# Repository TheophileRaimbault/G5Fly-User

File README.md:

# G5Fly STM32G473

Open-source GNSS navigation board for drones and robotics.

G5Fly is a compact GNSS board built around the Septentrio Mosaic-G5 module and an STM32G473 microcontroller. This branch contains the STM32 hardware design and AP_Periph firmware configuration for DroneCAN integration.

Author: <a href="https://github.com/TheophileRaimbault">Théophile Raimbault</a><br>
Maintainer: Septentrio GNSS GitHub user <githubuser@septentrio.com><br>
External website: https://github.com/septentrio-gnss/G5Fly<br>
License: <a href="https://creativecommons.org/licenses/by-sa/4.0/">Creative Commons Attribution-ShareAlike 4.0</a> and <a href="https://www.oshwa.org/definition/">Open Source Hardware</a><br>

<div style="background-color:#e3f2fd; border-left:5px solid #1976D2; padding:10px; border-radius:5px; margin-top:10px;">
  ℹ️ <strong>Note:</strong> G5Fly is optimized for a 30.5 x 30.5 mm FPV drone form factor and is intended for open source drone or robot projects.
</div><br>

STM32 schematic: [Resources/G5Fly-schematics-STM32.pdf](Resources/G5Fly-schematics-STM32.pdf)

## Who is this repository for?

This project serves two audiences:

- Users who want to buy, assemble, or use the board as-is.
- Designers who want to understand the hardware in detail and create a custom version.

If you are a user, start with the sections below. If you want to modify the design, go to [DESIGN.md](DESIGN.md).

## For users

### Key features
- Compact 30.5 x 30.5 mm FPV-friendly form factor
- Septentrio Mosaic-G5 GNSS receiver support
- USB and external 5 V power options
- DroneCAN, TTL, serial and I2C interfaces
- Reset input and status LEDs
- STM32G473-based AP_Periph node with DroneCAN support

### Quick start
1. Use the current production design files in [hardware/versions/v1/kicad/production](hardware/versions/v1/kicad/production/) if you want to build the board without changing the design.
2. Connect a suitable GNSS antenna and power the board through USB or an external 5 V source.
3. Build and flash the AP_Periph firmware using the configuration in [firmware](firmware/).
4. Use the available UART, I2C, or DroneCAN interfaces depending on your integration target.
5. Validate the board with the status LEDs and the expected GNSS fix behavior before full integration.

### Antenna and power
- Power the board according to the STM32 schematic and the regulator design.
- Use an active antenna only with the voltage specified by the antenna manufacturer.
- Verify antenna power selection and connector wiring before powering the board.

<div style="background-color:#ffebee; border-left:5px solid #c62828; padding:10px; border-radius:5px; margin:10px 0;">
  <strong>Warning:</strong> Solder <code>JP1</code> before using an active antenna. If the jumper is left open, the <code>VANT</code> net is not powered and the antenna may not work, causing a significant loss of GNSS performance. Select only one voltage according to the antenna datasheet.
</div>

<table>
  <tr>
    <td align="center"><br><strong>3.3 V antenna</strong><br>Connect <code>VANT</code> to <code>+3.3V_RF</code>.</td>
    <td align="center"><br><strong>5 V antenna</strong><br>Connect <code>VANT</code> to <code>+5V</code>.</td>
  </tr>
</table>

### Production and manufacturing
For a production build without hardware changes:

- Use the current KiCad project and generated manufacturing files from the hardware folder: [hardware/versions/v1/kicad](hardware/versions/v1/kicad/)
- Provide the manufacturer with the schematic, PCB files, BOM, and CPL.
- Verify antenna connector type, jumper configuration, and power options before assembly.
- Reference schematic: [Resources/G5Fly-schematics-STM32.pdf](Resources/G5Fly-schematics-STM32.pdf)

#### JLCPCB manufacturing requirements

- Keep the default KiCad PCB setup and its calculated impedance settings.
- Manufacture the board as a 6-layer PCB.
- `PCB Requirement: User.1 layer should be used as the V-cut guide layer.`
- Refer to the PCB design rules in [hardware/common/design_rules/design-rules.md](hardware/common/design_rules/design-rules.md) when preparing or reviewing the PCB for production.
- Use the [G5Fly_STM32_Rev2_JLCPCB production archive](hardware/versions/v1/kicad/production/G5Fly_STM32_Rev2_JLCPCB.zip) for the files prepared specifically for manufacturing at JLCPCB.

### Power and antenna
- Keep GNSS antenna cables away from noisy power traces where possible.

### Recommended antenna options
The following antenna families are commonly considered for evaluation:

- D-Helix antenna HX-CHX600A
- D-Helix antenna HX-CH7609A
- HC990EXF Calian antenna

A SMA-to-MMCX adapter is often useful for compatibility with the board connector.

## For designers and contributors

The detailed hardware design guide is available in [DESIGN.md](DESIGN.md).

That document covers:
- Overall architecture and major blocks
- Component selection and board organization
- How to create a custom derivative board
- Manufacturing and validation recommendations
- AP_Periph firmware configuration and DroneCAN bring-up

## Repository structure
- [hardware](hardware): PCB sources, KiCad projects, and mechanical assets
- [firmware](firmware): firmware and configuration files
- [Resources](Resources): images, schematics, and support documents
- [firmware/DroneCAN-Setup.md](firmware/DroneCAN-Setup.md): AP_Periph, DroneCAN, Mission Planner, and debugging procedure

## Licensing
This project is released under the Creative Commons Attribution-ShareAlike 4.0 license and follows the Open Source Hardware definition.

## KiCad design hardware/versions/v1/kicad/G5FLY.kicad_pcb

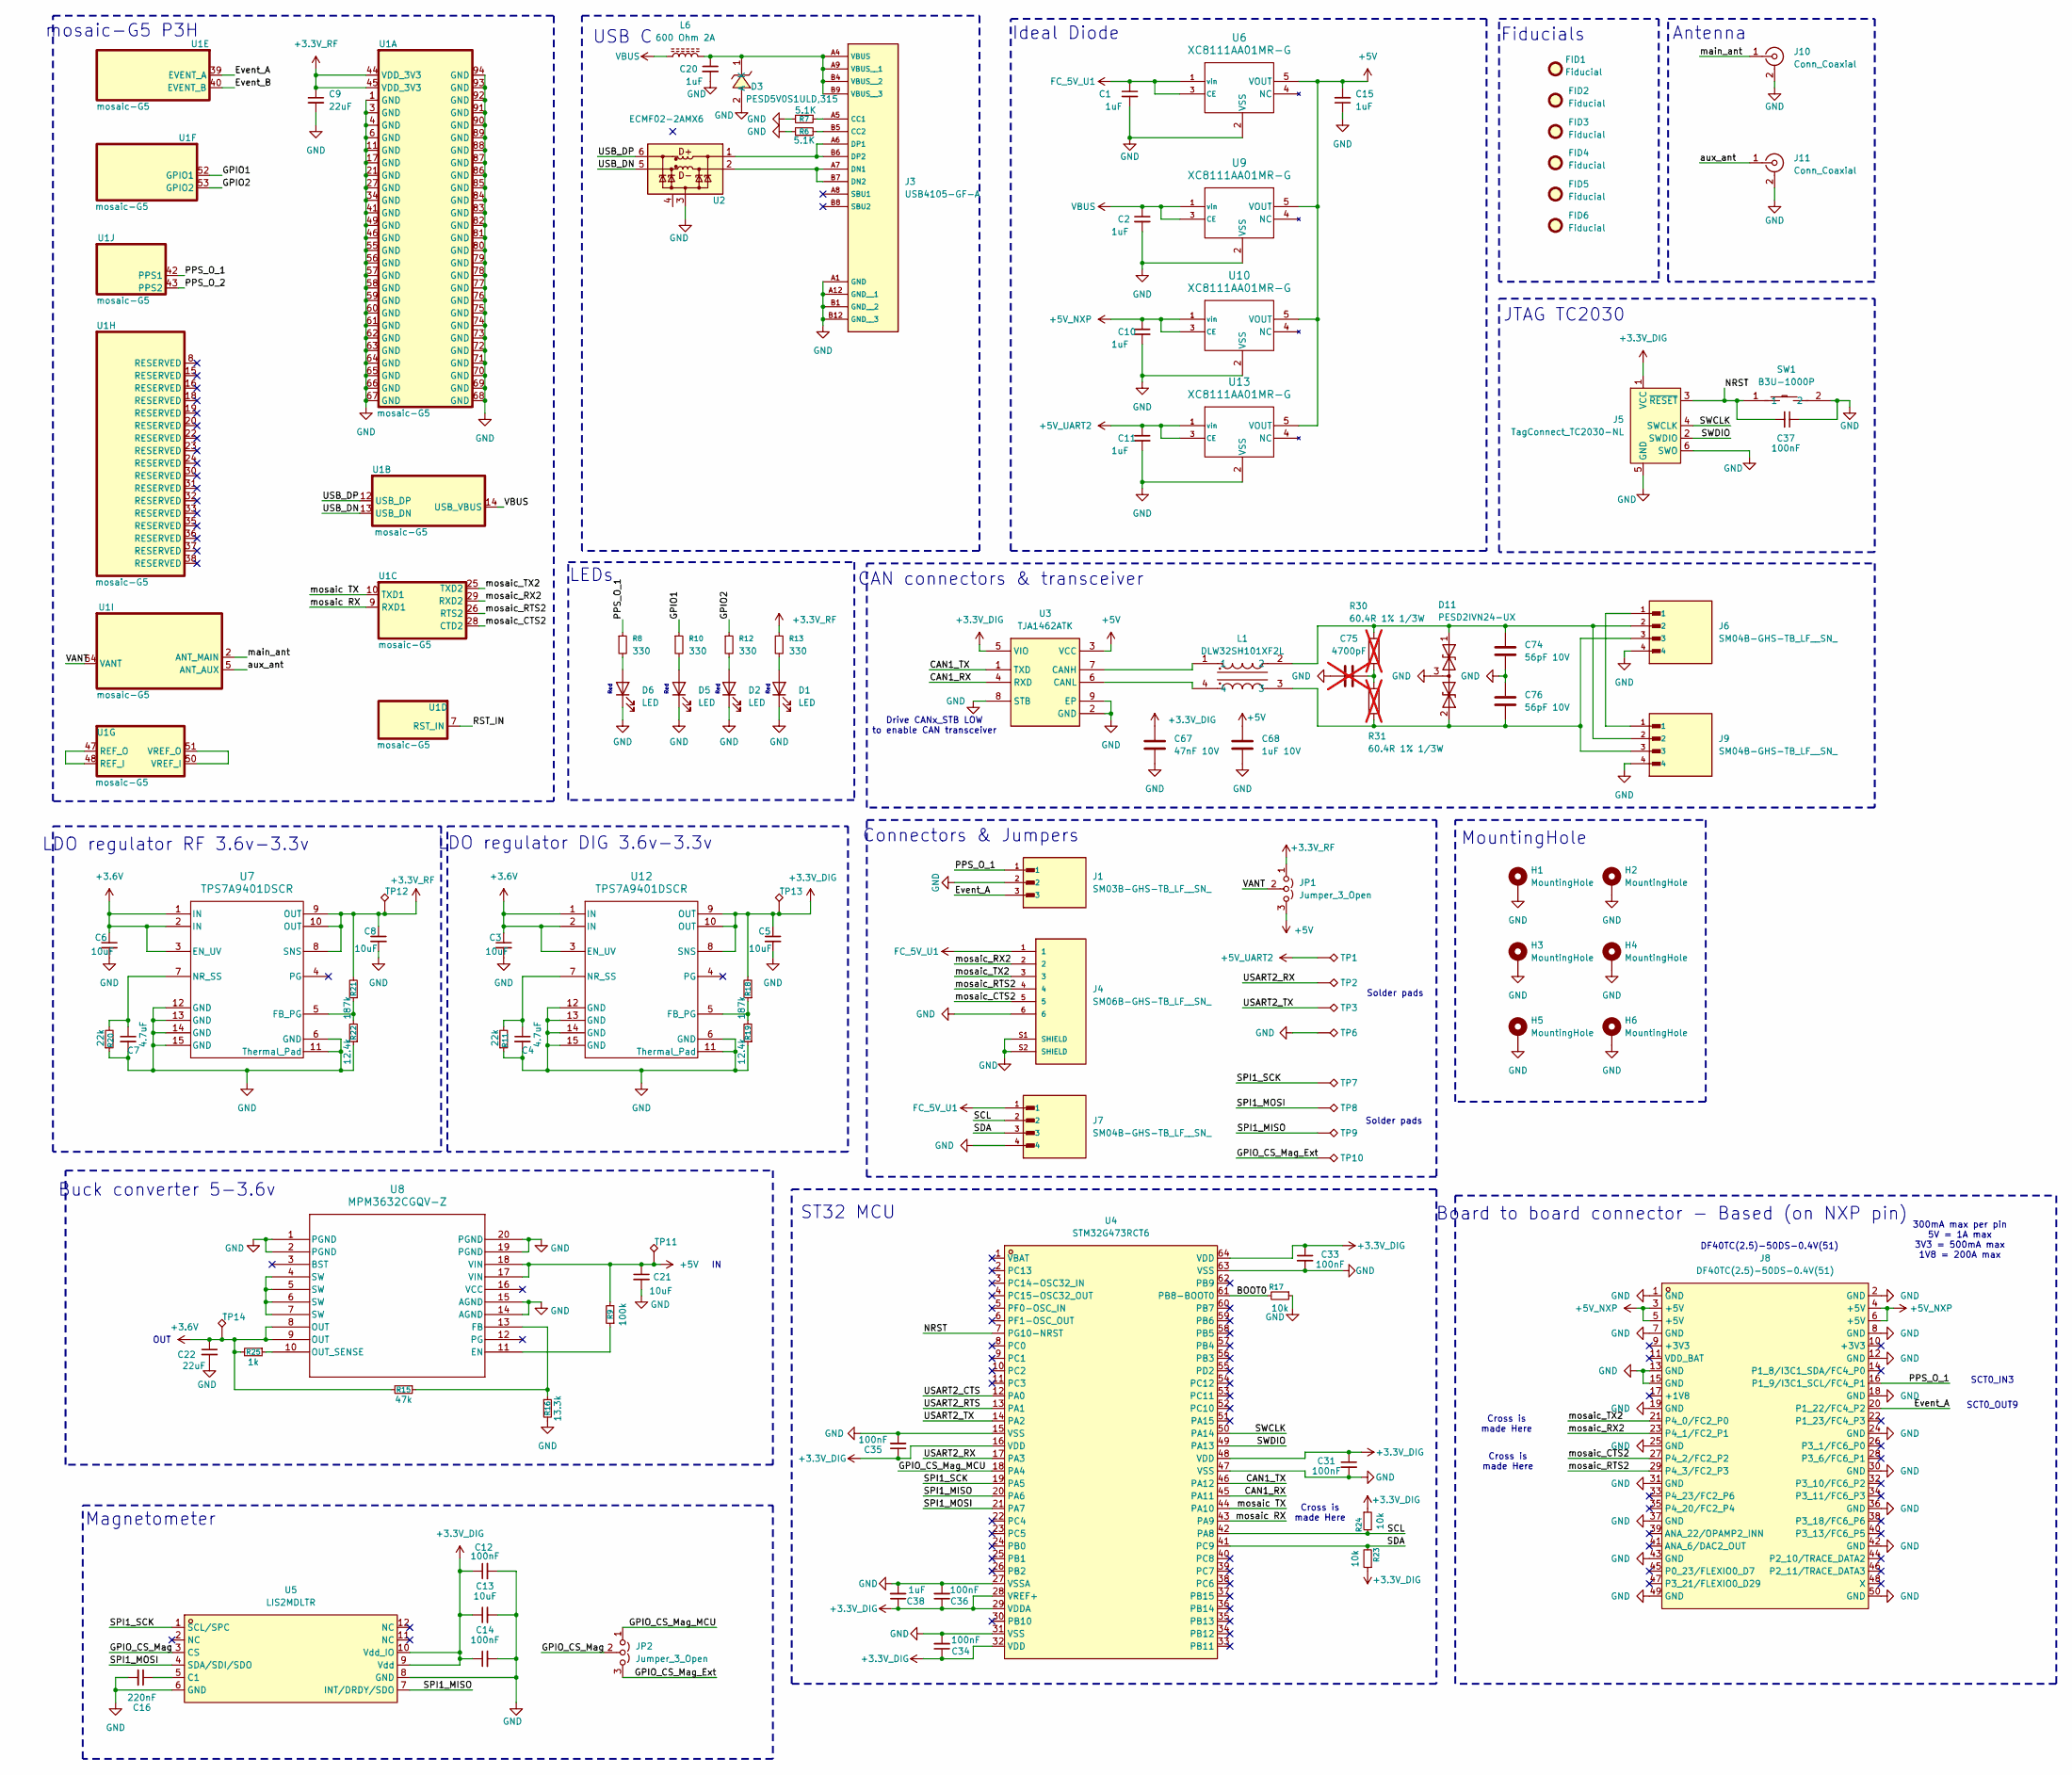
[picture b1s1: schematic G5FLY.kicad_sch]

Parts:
C1, C2, C10, C11, C15, C20, C38: 1uF; C_0402_1005Metric
C3, C5, C6, C8, C21: 10uF; C_0603_1608Metric
C4: 4.7uF; C_0402_1005Metric
C7: 4.7uF; C_0603_1608Metric
C9, C22: 22uF; C_0805_2012Metric
C12, C14, C31, C33, C34, C35, C36, C37: 100nF; C_0402_1005Metric
C13: 10uF; C_0402_1005Metric
C16: 220nF; C_0402_1005Metric
C67: 47nF 10V; C_0402_1005Metric; JLCPCB C77012
C68: 1uF 10V; C_0402_1005Metric; JLCPCB C528974
C74, C76: 56pF 10V; C_0402_1005Metric; JLCPCB C107007
C75: 4700pF; C_0402_1005Metric; DigiKey 311-1418-1-ND; not fitted
D1, D2, D5, D6: LED; LED_0402_1005Metric
D3: PESD5V0S1ULD,315; SOD-882_L1.0-W0.6-RD; MPN PESD5V0S1ULD,315; LCSC Part C552570
D11: PESD2IVN24-UX; SOT-323_SC-70; JLCPCB C552496
FID1, FID2, FID3, FID4, FID5, FID6: Fiducial; Fiducial_0.5mm_Mask1mm
H1, H2, H3, H4, H5, H6: MountingHole; MountingHole_3.2mm_M3_DIN965_Pad
J1: SM03B-GHS-TB_LF__SN_; JST_SM03B-GHS-TB_LF__SN_
J3: USB4105-GF-A; USB_C_Receptacle_GCT_USB4105-xx-A_16P_TopMnt_Horizontal
J4: SM06B-GHS-TB_LF__SN_; JST_SM06B-GHS-TB_LF__SN_; PARTREV N/A
J5: TagConnect_TC2030-NL; Tag-Connect_TC2030-IDC-NL_2x03_P1.27mm_Vertical
J6, J7, J9: SM04B-GHS-TB_LF__SN_; JST_SM04B-GHS-TB_LF__SN_
J8: DF40TC(2.5)-50DS-0.4V(51); CONN-SMD_DF40C-50DS-0.4V51; MPN DF40C-50DS-0.4V(51); LCSC Part C424646
J10, J11: Conn_Coaxial; SAMTEC_MMCX-J-P-H-RA-TH1
JP1, JP2: Jumper_3_Open; SolderJumper-3_P1.3mm_Open_Pad1.0x1.5mm_NumberLabels
L1: DLW32SH101XF2L; FILTER-SMD_4P-L3.2-W2.5-BL_DLW32SH510XK2L; MPN DLW32SH101XF2L; LCSC Part C1857795
L6: 600 Ohm 2A; L_0603_1608Metric; DigiKey 445-MPZ2012S601ATD25CT-ND
R6, R7: 5.1K; R_0402_1005Metric
R8, R10, R12, R13: 330; R_0402_1005Metric
R9: 100k; R_0402_1005Metric
R11, R20: 22k; R_0402_1005Metric
R15: 47k; R_0402_1005Metric
R16: 13.3k; R_0402_1005Metric
R17, R23, R24: 10k; R_0402_1005Metric
R18, R21: 187k; R_0402_1005Metric
R19, R22: 12.4k; R_0402_1005Metric
R25: 1k; R_0402_1005Metric
R30, R31: 60.4R 1% 1/3W; R_0603_1608Metric; DigiKey 541-60.4SCT-ND; not fitted
SW1: B3U-1000P; KEY-SMD_B3U-1000PM; MPN B3U-1000P; LCSC Part C231329
TP1, TP2, TP3, TP6, TP7, TP8, TP9, TP10: TestPoint_Alt; TestPoint_Pad_1.5x1.5mm
TP11, TP12, TP13, TP14: TestPoint_Alt; TestPoint_Pad_D1.0mm
U1: mosaic-G5; LGA54_MOSAIC-MINI_SEP
U2: ECMF02-2AMX6; ST_UQFN-6L_1.5x1.7mm_P0.5mm
U3: TJA1462ATK; SON65P300X300X100-9N-D; JLCPCB C3229259
U4: STM32G473RCT6; LQFP-64_L10.0-W10.0-P0.50-LS12.0-BL; MPN STM32G473RCT6; LCSC Part C529361
U5: LIS2MDLTR; VLGA-12_L2.0-W2.0-P0.50-BL; MPN LIS2MDLTR; LCSC Part C919695
U6, U9, U10, U13: XC8111AA01MR-G; IC_XC8111AA01MR-G
U7, U12: TPS7A9401DSCR; DSC0010J-MFG
U8: MPM3632CGQV-Z; QFN3p0x5p0x1p6_MPM3632C_MNP

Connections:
+3.3V_DIG: C5.1, C12.1, C13.1, C14.1, C31.1, C33.1, C34.1, C35.1, C36.1, C38.1, C67.1, J5.1 (VCC), R18.2, R23.1, R24.1, TP13.1, U3.5 (VIO), U4.16 (VDD), U4.28 (VREF+), U4.29 (VDDA), U4.32 (VDD), U4.48 (VDD), U4.64 (VDD), U5.9 (Vdd), U5.10 (Vdd_IO), U12.8 (SNS), U12.9 (OUT), U12.10 (OUT); also elsewhere on the board
+3.3V_RF: C8.1, C9.1, JP1.1 (A), R13.1, R21.2, TP12.1, U1.44 (VDD_3V3), U1.45 (VDD_3V3), U7.8 (SNS), U7.9 (OUT), U7.10 (OUT); also elsewhere on the board
+3.6V: C3.1, C6.1, C22.1, R15.2, R25.2, TP14.1, U7.1 (IN), U7.2 (IN), U7.3 (EN_UV), U8.8 (OUT), U8.9 (OUT), U12.1 (IN), U12.2 (IN), U12.3 (EN_UV); also elsewhere on the board
+5V: C15.2, C21.1, C68.1, JP1.3 (B), R9.2, TP11.1 (1_1), U3.3 (VCC), U6.5 (VOUT), U8.17 (VIN), U8.18 (VIN), U9.5 (VOUT), U10.5 (VOUT), U13.5 (VOUT)
+5V_NXP: C10.1, J8.3 (+5V), J8.4 (+5V), J8.5 (+5V), J8.6 (+5V), U10.1 (vin), U10.3 (CE)
+5V_UART2: C11.1, TP1.1 (1_1), U13.1 (vin), U13.3 (CE)
/BOOT0: R17.2, U4.61 (PB8-BOOT0)
/CAN1_RX: U3.4 (RXD), U4.45 (PA11)
/CAN1_TX: U3.1 (TXD), U4.46 (PA12)
/Event_A: J1.3, J8.20 (P1_22/FC4_P2), U1.39 (EVENT_A)
/Event_B: U1.40 (EVENT_B)
/GPIO1: R10.1, U1.52 (GPIO1)
/GPIO2: R12.1, U1.53 (GPIO2)
/GPIO_CS_Mag: JP2.2 (C), U5.3 (CS)
/GPIO_CS_Mag_Ext: JP2.3 (B), TP10.1 (1_1)
/GPIO_CS_Mag_MCU: JP2.1 (A), U4.18 (PA4)
/NRST: C37.2, J5.3 (~RESET), SW1.1, U4.7 (PG10-NRST)
/PPS_O_1: J1.1, J8.16 (P1_9/I3C1_SCL/FC4_P1), R8.1, U1.42 (PPS1)
/PPS_O_2: U1.43 (PPS2)
/RST_IN: U1.7 (RST_IN)
/SCL: J7.2, R24.2, U4.42 (PA8)
/SDA: J7.3, R23.2, U4.41 (PC9)
/SPI1_MISO: TP9.1 (1_1), U4.20 (PA6), U5.7 (INT/DRDY/SDO)
/SPI1_MOSI: TP8.1 (1_1), U4.21 (PA7), U5.4 (SDA/SDI/SDO)
/SPI1_SCK: TP7.1 (1_1), U4.19 (PA5), U5.1 (SCL/SPC)
/SWCLK: J5.4 (SWCLK), U4.50 (PA14)
/SWDIO: J5.2 (SWDIO), U4.49 (PA13)
/USART2_CTS: U4.12 (PA0)
/USART2_RTS: U4.13 (PA1)
/USART2_RX: TP2.1 (1_1), U4.17 (PA3)
/USART2_TX: TP3.1 (1_1), U4.14 (PA2)
/USB_DN: U1.13 (USB_DN), U2.5 (D-_out)
/USB_DP: U1.12 (USB_DP), U2.6 (D+_out)
/VANT: JP1.2 (C), U1.54 (VANT)
/aux_ant: J11.1 (In), U1.5 (ANT_AUX)
/main_ant: J10.1 (In_1), U1.2 (ANT_MAIN)
/mosaic RX: U1.9 (RXD1), U4.43 (PA9)
/mosaic TX: U1.10 (TXD1), U4.44 (PA10)
/mosaic_CTS2: J4.5, J8.27 (P4_2/FC2_P2), U1.28 (CTD2)
/mosaic_RTS2: J4.4, J8.29 (P4_3/FC2_P3), U1.26 (RTS2)
/mosaic_RX2: J4.2, J8.23 (P4_1/FC2_P1), U1.29 (RXD2)
/mosaic_TX2: J4.3, J8.21 (P4_0/FC2_P0), U1.25 (TXD2)
FC_5V_U1: C1.1, J4.1, J7.1, U6.1 (vin), U6.3 (CE)
GND: C1.2, C2.2, C3.2, C4.2, C5.2, C6.2, C7.2, C8.2, C9.2, C10.2, C11.2, C12.2, C13.2, C14.2, C15.1, C16.2, C20.2, C21.2, C22.2, C31.2, C33.2, C34.2, C35.2, C36.2, C37.1, C38.2, C67.2, C68.2, C74.2, C75.1, C76.1, D1.1 (K), D2.1 (K), D3.2 (A), D5.1 (K), D6.1 (K), D11.3 (common), H1.1 (1_1), H2.1 (1_1), H3.1 (1_1), H4.1 (1_1), H5.1 (1_1), H6.1 (1_1), J1.2, J3.A1 (GND), J3.A12 (GND__1), J3.B1 (GND__2), J3.B12 (GND__3), J4.6, J4.S1 (SHIELD), J4.S2 (SHIELD), J5.5 (GND), J5.6 (SWO), J6.4, J7.4, J8.1 (GND), J8.2 (GND), J8.7 (GND), J8.8 (GND), J8.12 (GND), J8.13 (GND), J8.15 (GND), J8.18 (GND), J8.19 (GND), J8.24 (GND), J8.25 (GND), J8.30 (GND), J8.31 (GND), J8.36 (GND), J8.37 (GND), J8.42 (GND), J8.43 (GND), J8.49 (GND), J8.50 (GND), J9.4, J10.2 (Ext), J11.2 (Ext), R6.1, R7.2, R11.1, R16.2, R17.1, R19.1, R20.1, R22.1, SW1.2, TP6.1 (1_1), U1.1 (GND), U1.3 (GND), U1.4 (GND), U1.6 (GND), U1.11 (GND), U1.17 (GND), U1.21 (GND), U1.27 (GND), U1.34 (GND), U1.41 (GND), U1.46 (GND), U1.49 (GND), U1.55 (GND), U1.56 (GND), U1.57 (GND), U1.58 (GND), U1.59 (GND), U1.60 (GND), U1.61 (GND), U1.62 (GND), U1.63 (GND), U1.64 (GND), U1.65 (GND), U1.66 (GND), U1.67 (GND), U1.68 (GND), U1.69 (GND), U1.70 (GND), U1.71 (GND), U1.72 (GND), U1.73 (GND), U1.74 (GND), U1.75 (GND), U1.76 (GND), U1.77 (GND), U1.78 (GND), U1.79 (GND), U1.80 (GND), U1.81 (GND), U1.82 (GND), U1.83 (GND), U1.84 (GND), U1.85 (GND), U1.86 (GND), U1.87 (GND), U1.88 (GND), U1.89 (GND), U1.90 (GND), U1.91 (GND), U1.92 (GND), U1.93 (GND), U1.94 (GND), U2.3 (GND), U3.2 (GND), U3.8 (STB), U3.9 (EP), U4.15 (VSS), U4.27 (VSSA), U4.31 (VSS), U4.47 (VSS), U4.63 (VSS), U5.6 (GND), U5.8 (GND), U6.2 (VSS), U7.6 (GND), U7.11 (Thermal_Pad), U7.12 (GND), U7.13 (GND), U7.14 (GND), U7.15 (GND), U8.1 (PGND), U8.2 (PGND), U8.14 (AGND), U8.15 (AGND), U8.19 (PGND), U8.20 (PGND), U9.2 (VSS), U10.2 (VSS), U12.6 (GND), U12.11 (Thermal_Pad), U12.12 (GND), U12.13 (GND), U12.14 (GND), U12.15 (GND), U13.2 (VSS)
unnamed: C75.2, R30.2, R31.1
unnamed: D1.2 (A), R13.2
unnamed: D2.2 (A), R12.2
unnamed: C20.1, D3.1 (K), J3.A4 (VBUS), J3.A9 (VBUS__1), J3.B4 (VBUS__2), J3.B9 (VBUS__3), L6.2
unnamed: D5.2 (A), R10.2
unnamed: D6.2 (A), R8.2
unnamed: C74.1, D11.1 (A1), J6.2, J9.2, L1.2, R30.1
unnamed: C76.2, D11.2 (A2), J6.3, J9.3, L1.3, R31.2
unnamed: J3.A5 (CC1), R7.1
unnamed: J3.B5 (CC2), R6.2
unnamed: J3.A7 (DN1), J3.B7 (DN2), U2.2 (D-_in)
unnamed: J3.A6 (DP1), J3.B6 (DP2), U2.1 (D+_in)
unnamed: J6.1, J9.1
unnamed: U1.47 (REF_O), U1.48 (REF_I)
unnamed: U1.50 (VREF_I), U1.51 (VREF_O)
unnamed: L1.1, U3.7 (CANH)
unnamed: L1.4, U3.6 (CANL)
unnamed: C16.1, U5.5 (C1)
unnamed: R21.1, R22.2, U7.5 (FB_PG)
unnamed: C7.1, R20.2, U7.7 (NR_SS)
unnamed: R9.1, U8.11 (EN)
unnamed: R15.1, R16.1, U8.13 (FB)
unnamed: R25.1, U8.10 (OUT_SENSE)
unnamed: U8.4 (SW), U8.5 (SW), U8.6 (SW), U8.7 (SW)
unnamed: R18.1, R19.2, U12.5 (FB_PG)
unnamed: C4.1, R11.2, U12.7 (NR_SS)
VBUS: C2.1, L6.1, U1.14 (USB_VBUS), U9.1 (vin), U9.3 (CE)

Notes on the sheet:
DF40TC(2.5)-50DS-0.4V(51)
Fiducials
CAN connectors & transceiver
ST32 MCU
Connectors & Jumpers
Cross is made Here
LDO regulator DIG 3.6v-3.3v
Solder pads
mosaic-G5 P3H
Board to board connector - Based (on NXP pin)
LDO regulator RF 3.6v-3.3v
OUT
Red
Drive CANx_STB LOW to enable CAN transceiver
Buck converter 5-3.6v
Ideal Diode
USB C
300mA max per pin 5V = 1A max 3V3 = 500mA max 1V8 = 200A max
SCT0_OUT9
Antenna
JTAG TC2030
LEDs
MountingHole
SCT0_IN3
Magnetometer

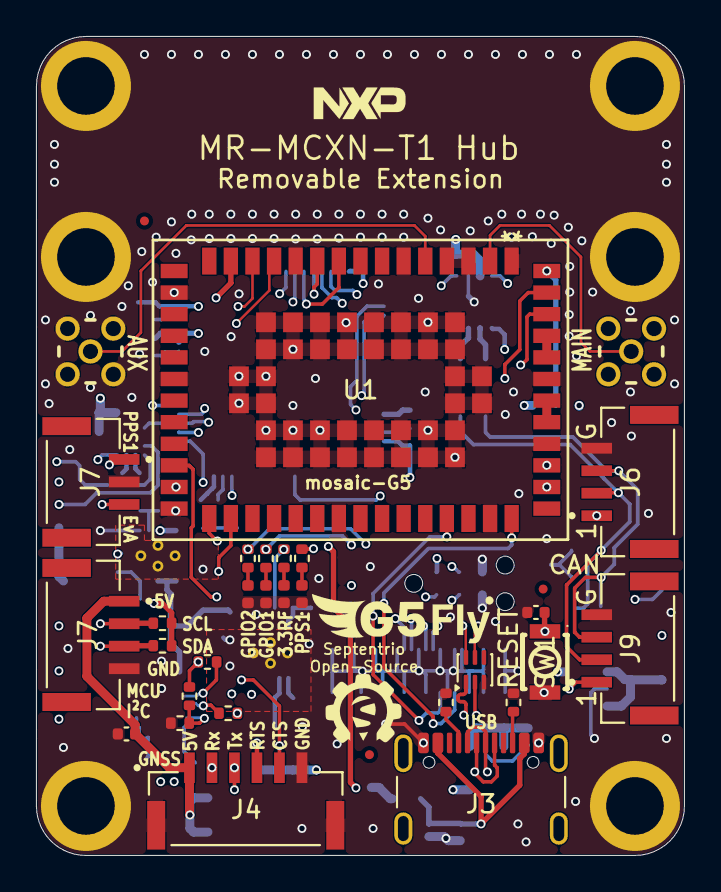
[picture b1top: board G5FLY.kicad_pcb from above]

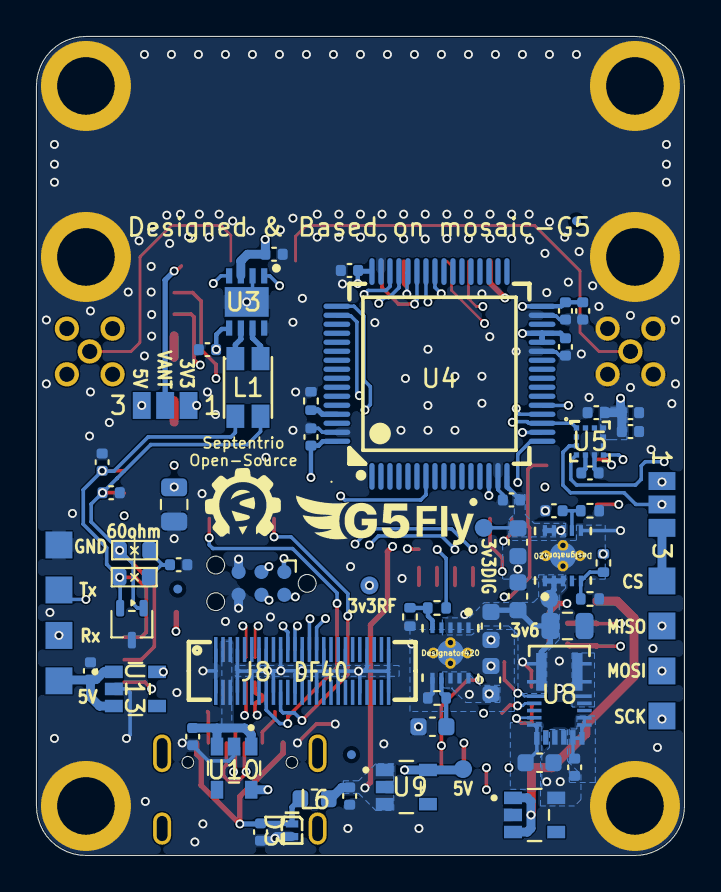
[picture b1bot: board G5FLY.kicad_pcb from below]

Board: 6 copper layers, 36.0 x 45.5 mm, 109 parts (71 on the bottom side), 66 nets.

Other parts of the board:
3.3DIG, 3.3RF, 3.6V: TestPoint_Alt; TestPoint_Pad_D1.0mm

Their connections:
+3.3V_DIG: 3.3DIG.1 (1_1); also elsewhere on the board
+3.3V_RF: 3.3RF.1 (1_1); also elsewhere on the board
+3.6V: 3.6V.1 (1_1); also elsewhere on the board

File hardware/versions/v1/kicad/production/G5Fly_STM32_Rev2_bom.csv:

Designator,Footprint,Quantity,Value,LCSC Part #
"3.3DIG, 3.3RF, 3.6V, TP11",TestPoint_Pad_D1.0mm,4,TestPoint_Alt,
"C1, C10, C11, C15, C2, C20, C38",0402,7,1uF,
"C12, C14, C31, C33, C34, C35, C36, C37",0402,8,100nF,
C13,0402,1,10uF,
C16,0402,1,220nF,
"C21, C3, C5, C6, C8",0603,5,10uF,
"C22, C9",0805,2,22uF,
C4,0402,1,4.7uF,
C67,0402,1,47nF 10V,
C68,0402,1,1uF 10V,
C7,0603,1,4.7uF,
"C74, C76",0402,2,56pF 10V,
C75,0402,1,4700pF,
"D1, D2, D5, D6",0402,4,LED,
D11,SOT-323_SC-70,1,PESD2IVN24-UX,
D3,SOD-882_L1.0-W0.6-RD,1,"PESD5V0S1ULD,315",C552570
J1,JST_SM03B-GHS-TB_LF__SN_,1,SM03B-GHS-TB_LF__SN_,
"J10, J11",SAMTEC_MMCX-J-P-H-RA-TH1,2,Conn_Coaxial,
J3,USB_C_Receptacle_GCT_USB4105-xx-A_16P_TopMnt_Horizontal,1,USB4105-GF-A,
J4,JST_SM06B-GHS-TB_LF__SN_,1,SM06B-GHS-TB_LF__SN_,
"J6, J7, J9",JST_SM04B-GHS-TB_LF__SN_,3,SM04B-GHS-TB_LF__SN_,
J8,CONN-SMD_DF40C-50DS-0.4V51,1,DF40C-50DS-0.4V,C424646
L1,FILTER-SMD_4P-L3.2-W2.5-BL_DLW32SH510XK2L,1,DLW32SH101XF2L,C1857795
L6,0603,1,600 Ohm 2A,
"R10, R12, R13, R8",0402,4,330,
"R11, R20",0402,2,22k,
R15,0402,1,47k,
R16,0402,1,24k,
"R17, R23, R24",0402,3,10k,
"R18, R21",0402,2,187k,
"R19, R22",0402,2,12.4k,
R25,0402,1,1k,
"R30, R31",0603,2,60.4R 1% 1/3W,
"R6, R7",0402,2,5.1K,
R9,0402,1,100k,
SW1,KEY-SMD_B3U-1000PM,1,B3U-1000P,C231329
"TP1, TP10, TP2, TP3, TP6, TP7, TP8, TP9",TestPoint_Pad_1.5x1.5mm,8,TestPoint_Alt,
U1,LGA54_MOSAIC-MINI_SEP,1,mosaic-G5,
"U10, U13, U6, U9",IC_XC8111AA01MR-G,4,XC8111AA01MR-G,
"U12, U7",DSC0010J-MFG,2,TPS7A9401DSCR,
U2,ST_UQFN-6L_1.5x1.7mm_P0.5mm,1,ECMF02-2AMX6,
U3,SON65P300X300X100-9N-D,1,TJA1462ATK,
U4,LQFP-64_L10.0-W10.0-P0.50-LS12.0-BL,1,STM32G473RCT6,C529361
U5,VLGA-12_L2.0-W2.0-P0.50-BL,1,LIS2MDLTR,C919695
U8,QFN3p0x5p0x1p6_MPM3632C_MNP,1,MPM3632CGQV-Z,

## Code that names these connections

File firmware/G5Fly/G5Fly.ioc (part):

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Mcu.Name=STM32G473R(B-C-E)Tx
Mcu.Package=LQFP64
Mcu.UserName=STM32G473RCTx
PA10.Mode=Asynchronous
PA10.Signal=USART1_RX
PA11.Mode=FDCAN_Activate
PA11.Signal=FDCAN1_RX
PA12.Mode=FDCAN_Activate
PA12.Signal=FDCAN1_TX
PA13.Mode=Serial_Wire
PA13.Signal=SYS_JTMS-SWDIO
PA14.Mode=Serial_Wire
PA14.Signal=SYS_JTCK-SWCLK
PA2.Mode=Asynchronous
PA2.Signal=LPUART1_TX
PA3.Mode=Asynchronous
PA3.Signal=LPUART1_RX
PA4.GPIOParameters=GPIO_Speed,PinState
PA4.GPIO_Speed=GPIO_SPEED_FREQ_HIGH
PA4.PinState=GPIO_PIN_SET
PA4.Signal=GPIO_Output
PA5.Mode=Full_Duplex_Master
PA5.Signal=SPI1_SCK
PA6.Mode=Full_Duplex_Master
PA6.Signal=SPI1_MISO
PA7.Mode=Full_Duplex_Master
PA7.Signal=SPI1_MOSI
PA8.Mode=I2C
PA8.Signal=I2C3_SCL
PA9.Mode=Asynchronous
PA9.Signal=USART1_TX
PC9.Mode=I2C
PC9.Signal=I2C3_SDA
RCC.HSE_VALUE=8000000
RCC.SYSCLKFreq_VALUE=170000000
RCC.SYSCLKSource=RCC_SYSCLKSOURCE_PLLCLK
board=custom
